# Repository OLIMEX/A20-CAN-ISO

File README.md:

# A20-CAN-ISO
Galvanic insulated CAN dreiver for A20-OLinuXino Small Linux Computers

Product page: https://www.olimex.com/Products/OLinuXino/A20/A20-CAN-ISO/open-source-hardware

# License
- Hardware is with CERN OHL v1.2 license
- Software is with GPL3 license
- Documentation is with CC BY-SA 4.0 license

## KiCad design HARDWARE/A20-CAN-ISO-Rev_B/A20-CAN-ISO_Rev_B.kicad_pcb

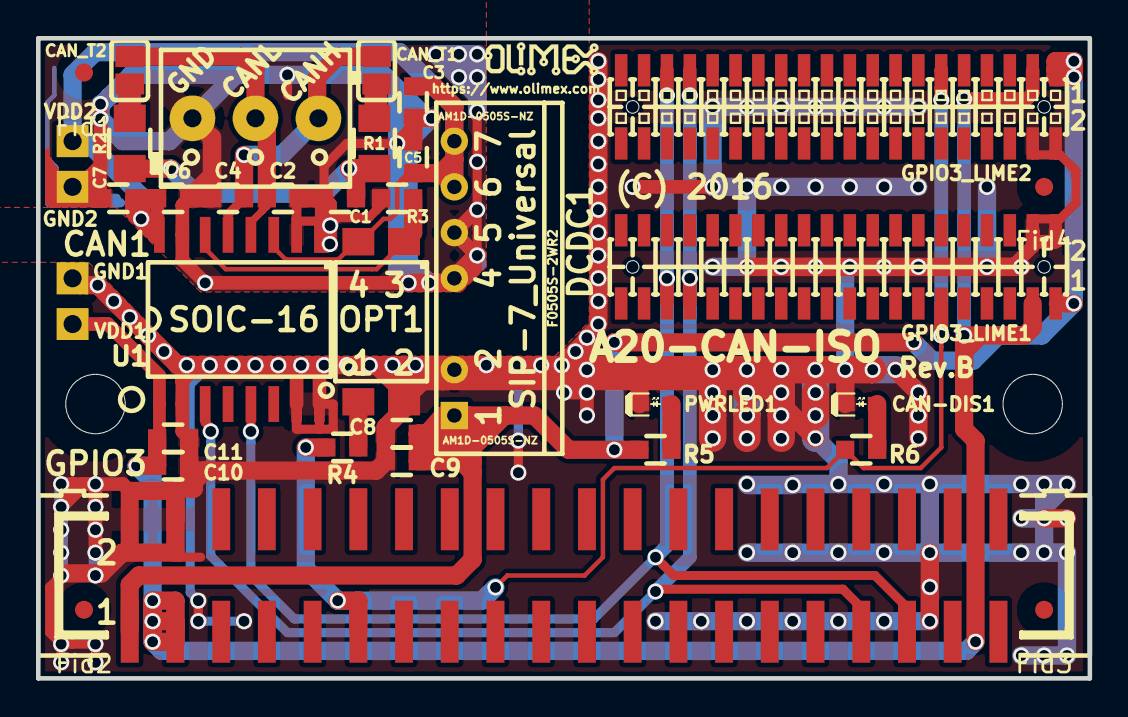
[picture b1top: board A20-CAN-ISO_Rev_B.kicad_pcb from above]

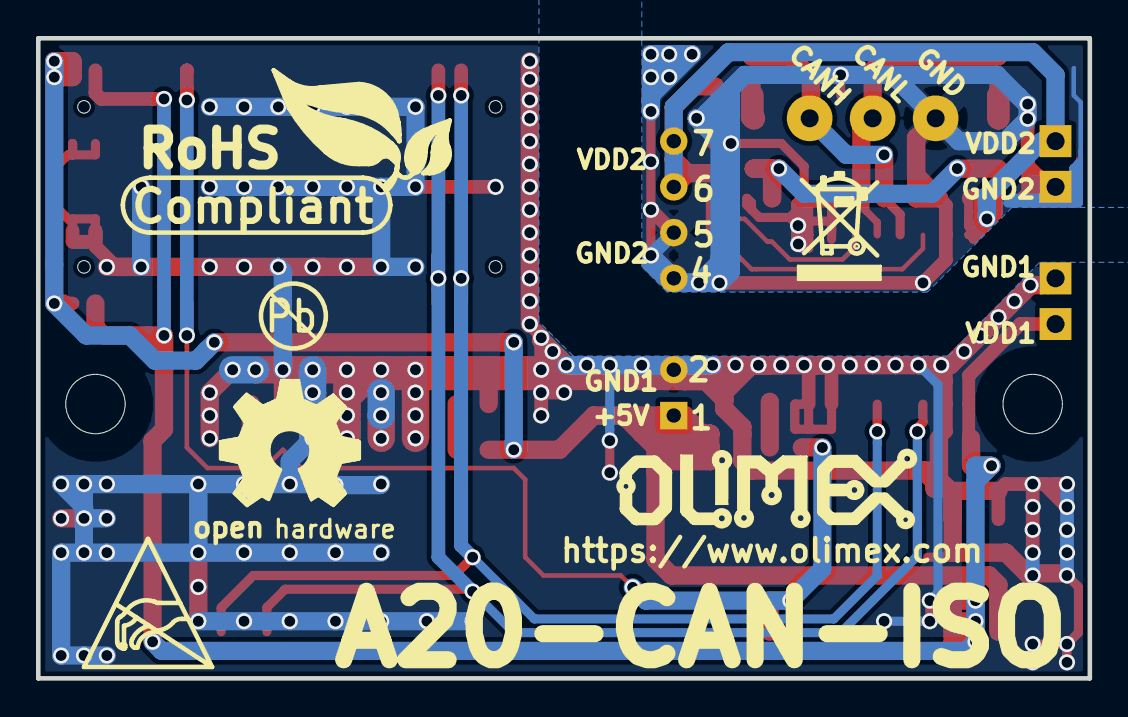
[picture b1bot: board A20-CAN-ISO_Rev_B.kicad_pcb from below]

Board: 2 copper layers, 58.4 x 35.6 mm, 45 parts (6 on the bottom side), 17 nets.

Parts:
C1: 4.7nF; C_0603_5MIL_DWS
C2, C4: 47pF; C_0603_5MIL_DWS
C3, C6, C8, C10: 100nF; C_0603_5MIL_DWS
C5, C7, C9, C11: 10uF/6.3V/0603; C_0603_5MIL_DWS
CAN1: TB3-3.5mm
CAN-DIS1: NA(LED/Red/0603); LED_0603_KA
CAN_T1, CAN_T2: Opened; SJ
DCDC1: F0505S-2WR2(SIP-7_Universal); SIP-7_Universal
Fid1, Fid2, Fid3, Fid4: Fiducial1x3
GND1, GND2: TESTPAD; TEST_PAD40x70_SQUARE
GPIO3: GBH-254-SMT-40; GBH-254-SMT-40_Shorten_Pads
GPIO3_LIME1: PA-V16X-2X20-LF; GPCB127SMT-02X20(YA-V36P-2X20-LF)
GPIO3_LIME2: PA-V16X-2X20-LF; GPH127SMT-02X20(PA-V16X-2X20-LF)
Logo-Olimex: LOGO_OLIMEX_80
Logo_Olimex: OLIMEX_LOGO_TB
MountingHole1, MountingHole2: Mounting_hole_3.3mm
OPT1: NA(H11A817C_SMD(PC817X3NIP06)); H11A817C_SMD(PC817X3NIP06)_FP
PWRLED1: LED/Red/0603; LED_0603_KA
R1, R2: 60.4R/1%; R_1206_5MIL_DWS
R3: 10k; R_0603_5MIL_DWS
R4: NA(220R); R_0603_5MIL_DWS
R5: 2.2k; R_0603_5MIL_DWS
R6: NA(2.2k); R_0603_5MIL_DWS
Sign_Antistatic: Val**; LOGO_ANTISTATIC_1
Sign_OSHW: LOGO_OPENHARDWARE_8x8
Sign_Pb-Free: LOGO_PBFREE
Sign_RecycleBin: LOGO_RECYCLEBIN_1
Sign_RoHS: Val**; LOGO_ROHS_1
U1: TJA1052IT/5Y(SOIC-16_300mil); SOIC-16_300mil
VDD1, VDD2: TESTPAD; TEST_PAD40x70_SQUARE

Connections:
+3V3: C10.2, C11.2, GPIO3.3, GPIO3_LIME1.3, GPIO3_LIME2.3, U1.1, VDD1.1
+5V: C8.2, C9.2, DCDC1.1, GPIO3.1, GPIO3_LIME1.1, GPIO3_LIME2.1, R5.1
+5VP: C3.2, C5.2, C6.2, C7.2, DCDC1.6, DCDC1.7, OPT1.4, U1.11, U1.16, VDD2.1
/CAN-CTRL: GPIO3.11, GPIO3_LIME1.11, GPIO3_LIME2.11, R4.2, R6.1
/CAN-RX: GPIO3.35, GPIO3_LIME1.35, GPIO3_LIME2.35, U1.5
/CAN-TX: GPIO3.33, GPIO3_LIME1.33, GPIO3_LIME2.33, U1.3
/CANH: C4.2, CAN1.3, CAN_T1.2, U1.13
/CANL: C2.2, CAN1.2, CAN_T2.1, U1.12
Earth: C1.1, C2.1, C3.1, C4.1, C5.1, C6.1, C7.1, CAN1.1, DCDC1.4, DCDC1.5, GND2.1, R3.2, U1.9, U1.10, U1.15
GND: C8.1, C9.1, C10.1, C11.1, CAN-DIS1.1, DCDC1.2, GND1.1, GPIO3.2, GPIO3.4, GPIO3_LIME1.2, GPIO3_LIME1.4, GPIO3_LIME2.2, GPIO3_LIME2.4, OPT1.2, PWRLED1.1, U1.2, U1.7, U1.8
unnamed: C1.2, R1.2, R2.1
unnamed: CAN-DIS1.2, R6.2
unnamed: CAN_T1.1, R1.1
unnamed: CAN_T2.2, R2.2
unnamed: OPT1.1, R4.1
unnamed: OPT1.3, R3.1, U1.14
unnamed: PWRLED1.2, R5.2

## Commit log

2020-03-11 initial upload

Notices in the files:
HARDWARE/A20-CAN-ISO-Rev_B/A20-CAN-ISO_Rev_B.kicad_pcb:
(C) 2016
